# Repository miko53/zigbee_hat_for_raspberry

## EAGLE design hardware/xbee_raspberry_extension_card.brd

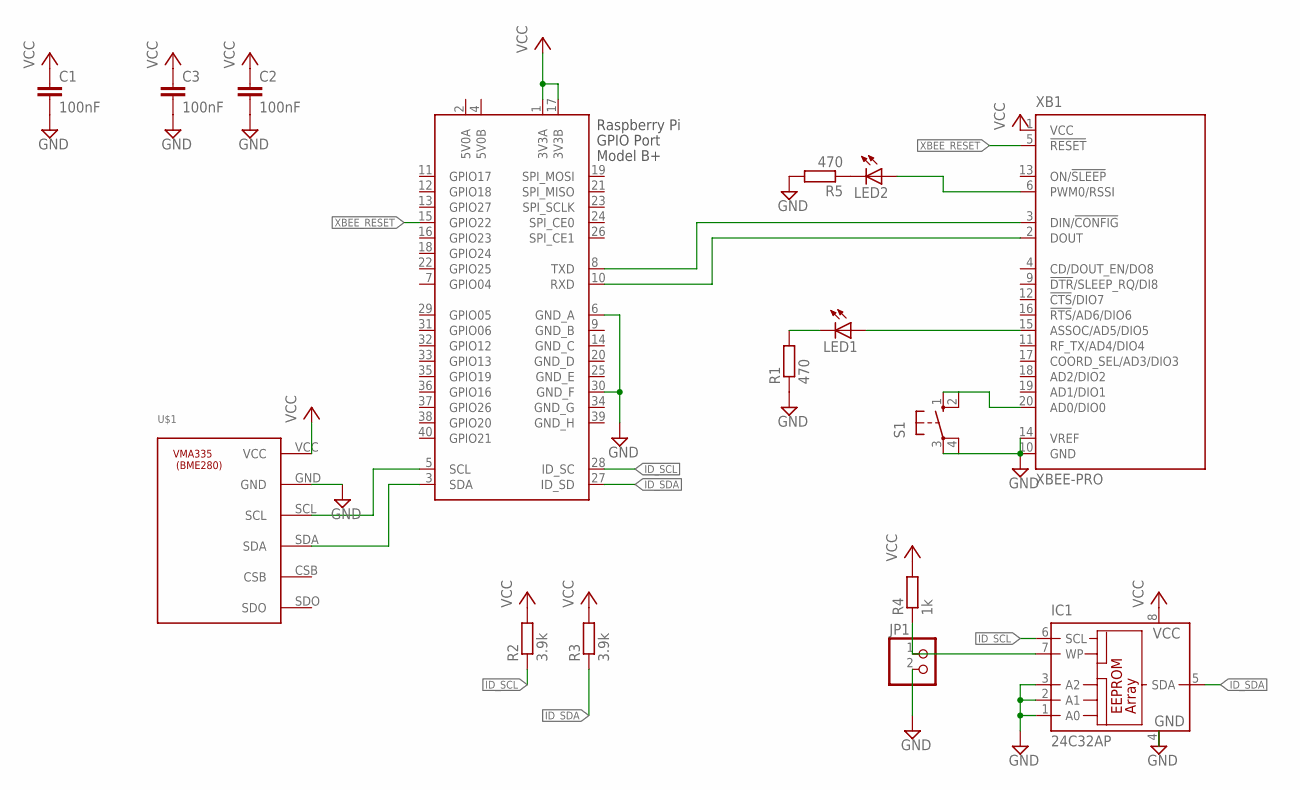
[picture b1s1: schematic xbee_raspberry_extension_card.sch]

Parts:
C1, C2, C3: 100nF; C050-030X075
IC1: 24C32AP; DIL8
JP1: PINHD-1X2; 1X02
LED1, LED2: LED3MM
R1, R5: 470; 0204/7
R2, R3: 3.9k; 0204/7
R4: 1k; 0204/7
S1: 10-XX; B3F-10XX
U$1: VMA335-BME280; VMA335_P
X1: RASPI_BOARD_B+#_HDC; RASPI_BOARD_B+HAT_DF_CF
XB1: XBEE-PRO

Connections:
5V0A: X1.2 (5V0A)
5V0B: X1.4 (5V0B)
GND: C1.2, C2.2, C3.2, IC1.1 (A0), IC1.2 (A1), IC1.3 (A2), IC1.4 (GND), JP1.2, R1.1, R5.2, S1.3, S1.4 (P1), U$1.GND, X1.6 (GND_A), X1.30 (GND_F), XB1.10 (GND), XB1.14 (VREF)
GND_B: X1.9 (GND_B)
GND_C: X1.14 (GND_C)
GND_D: X1.20 (GND_D)
GND_E: X1.25 (GND_E)
GND_G: X1.34 (GND_G)
GND_H: X1.39 (GND_H)
ID_SCL: IC1.6 (SCL), R2.1, X1.28 (ID_SC)
ID_SDA: IC1.5 (SDA), R3.1, X1.27 (ID_SD)
unnamed: X1.10 (RXD), XB1.2 (DOUT)
unnamed: X1.8 (TXD), XB1.3 (DIN/!CONFIG)
unnamed: U$1.SCL, X1.5 (SCL)
unnamed: U$1.SDA, X1.3 (SDA)
unnamed: IC1.7 (WP), JP1.1, R4.1
unnamed: LED1.A, XB1.15 (ASSOC/AD5/DIO5)
unnamed: LED1.K (C), R1.2
unnamed: S1.1 (S), S1.2 (S1), XB1.20 (AD0/DIO0)
unnamed: LED2.K (C), R5.1
unnamed: LED2.A, XB1.6 (PWM0/RSSI)
VCC: C1.1, C2.1, C3.1, IC1.8 (VCC), R2.2, R3.2, R4.2, U$1.VCC, X1.1 (3V3A), X1.17 (3V3B), XB1.1 (VCC)
XBEE_RESET: X1.15 (GPIO22), XB1.5 (!RESET)

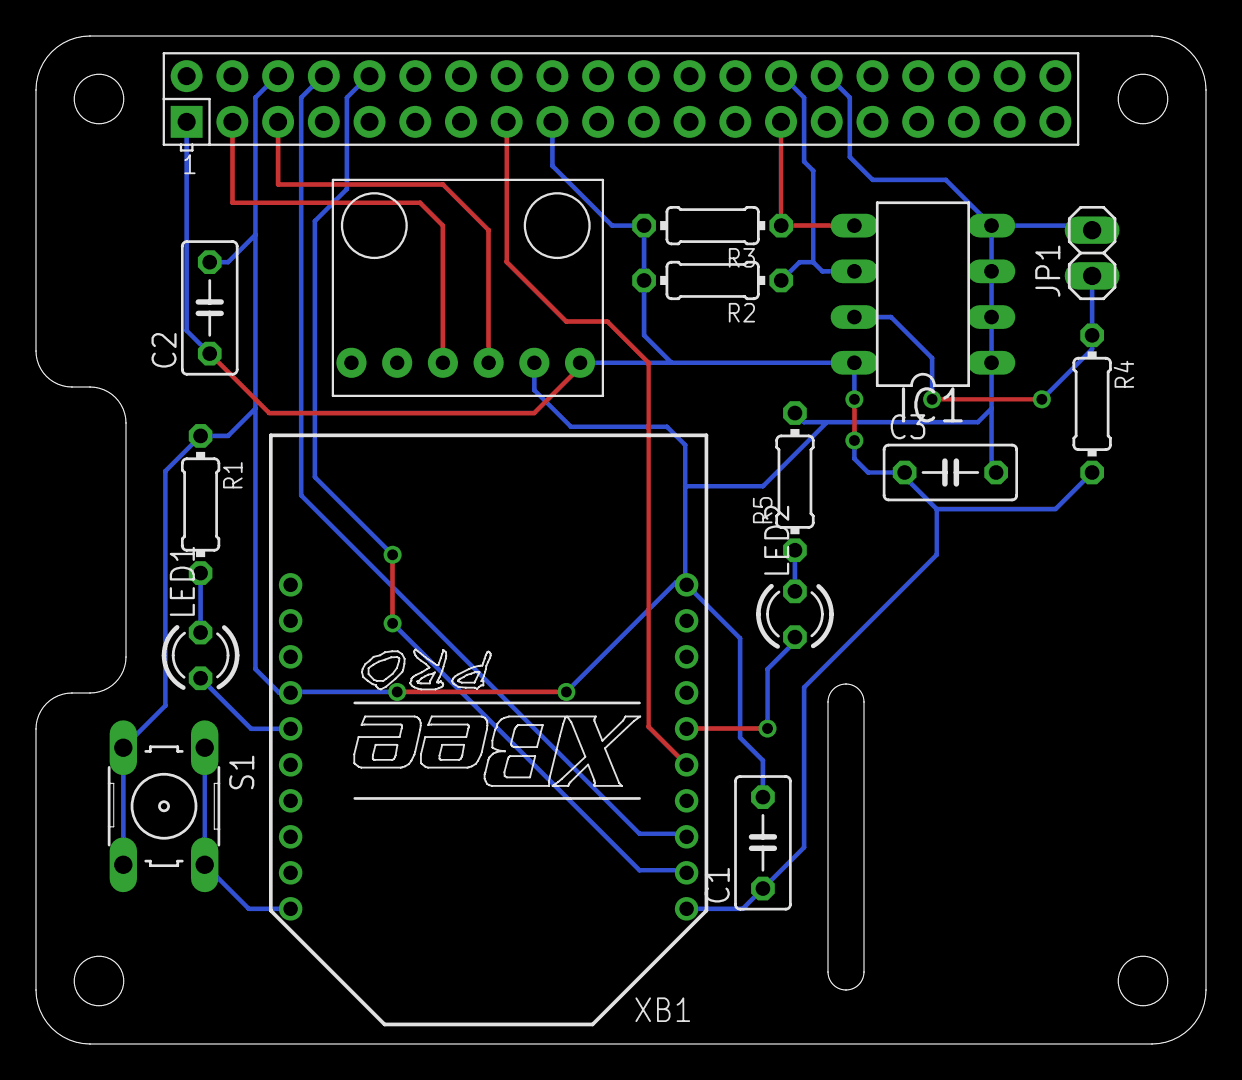
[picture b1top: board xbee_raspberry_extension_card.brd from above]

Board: 2 copper layers, 65.0 x 56.0 mm, 16 parts (0 on the bottom side), 15 nets.

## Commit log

2021-03-06 add schematic for zigbee HAT for raspberry PI
2021-03-06 add empty readme
2021-03-07 insert picture of board
2021-03-07 set picture in right side
2021-03-07 add EEPROM configuration and installation
2021-03-07 add another picture
2021-03-07 rename file
